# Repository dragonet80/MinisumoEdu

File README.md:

# MinisumoEdu
Robot de minisumo amb finalitats educatives.

De moment, hi ha els arxius en format Eagle de les plaques i les peces en 3D en format Sketchup.

Falten exemples software.
**Pendent de pujar tots els arxius i organitzar-ho tot**

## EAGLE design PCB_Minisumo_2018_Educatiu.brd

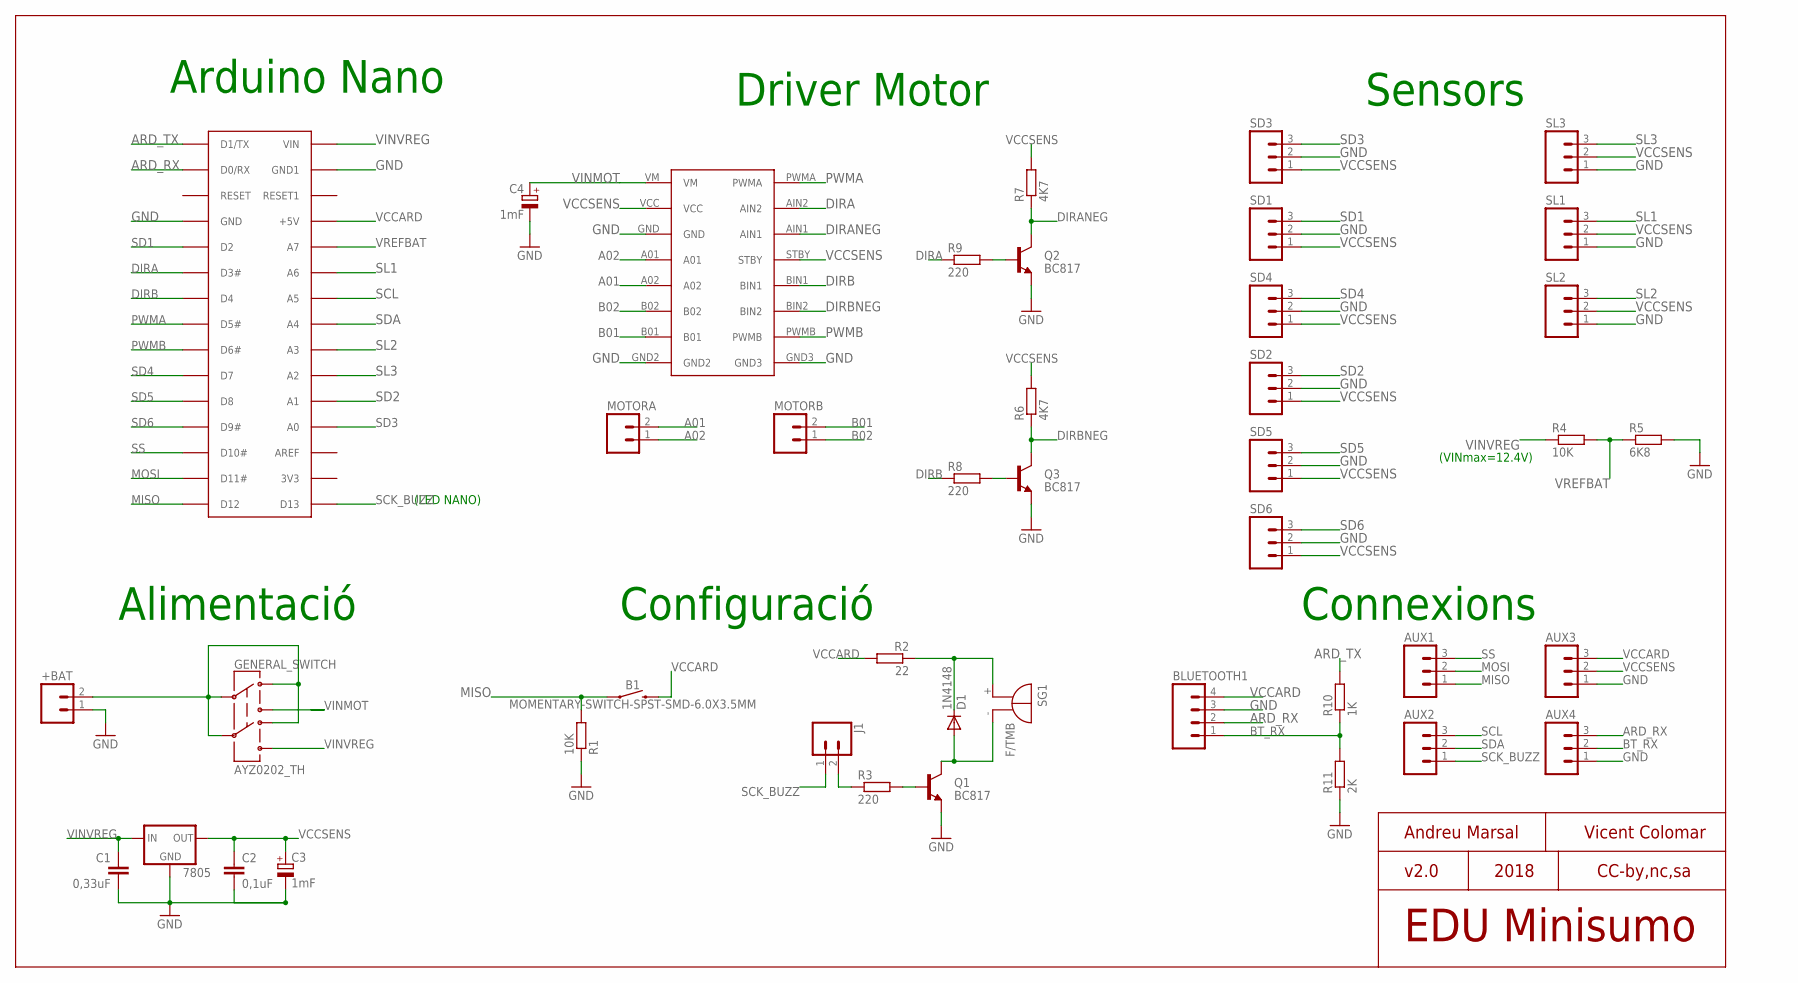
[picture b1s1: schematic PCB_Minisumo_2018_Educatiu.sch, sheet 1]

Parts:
7805: V_REG_78XXSINK; TO220-IGO
+BAT: M02LOCK_LONGPADS; 1X02_LOCK_LONGPADS
AUX1, AUX2, AUX3, AUX4: M03PTH; 1X03
B1: MOMENTARY-SWITCH-SPST-SMD-6.0X3.5MM; TACTILE_SWITCH_SMD_6.0X3.5MM
BLUETOOTH1: M04PTH; 1X04
C1: 0,33uF; C1206K
C2: 0,1uF; C1206K
C3, C4: 1mF; E2,5-6
D1: 1N4148; SOD106-R
GENERAL_SWITCH: AYZ0202_TH
J1: CONN_02; 1X02
MOTORA: M023.5MM; SCREWTERMINAL-3.5MM-2
MOTORB: M023.5MM; SCREWTERMINAL-3.5MM-2
Q1, Q2, Q3: BC817; TO-92
R1, R4: 10K; R1206
R2: 22; R1206
R3, R8, R9: 220; M1206
R5: 6K8; R1206
R6, R7: 4K7; M1206
R10: 1K; R1206
R11: 2K; R1206
SD1, SD2, SD3, SD4, SD5, SD6: M03PTH; 1X03
SG1: F/TMB
SL1, SL2, SL3: M03PTH; 1X03
U$1: ARDUINONANONOHOLES; PDIP-32NOHOLES
U$2: TB6612FNG_SPARKFUN

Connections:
A01: MOTORA.2, U$2.A02
A02: MOTORA.1, U$2.A01
ARD_RX: AUX4.3, BLUETOOTH1.2, U$1.D0/RX; also elsewhere on the board
ARD_TX: R10.2, U$1.D1/TX; also elsewhere on the board
B01: MOTORB.2, U$2.B01
B02: MOTORB.1, U$2.B02
BT_RX: AUX4.2, BLUETOOTH1.1, R10.1, R11.2
DIRA: R9.1, U$1.D3 (D3#), U$2.AIN2
DIRANEG: Q2.3 (C), R7.1, U$2.AIN1
DIRB: R8.1, U$1.D4, U$2.BIN1
DIRBNEG: Q3.3 (C), R6.1, U$2.BIN2
GND: 7805.GND, +BAT.1, AUX3.1, AUX4.1, BLUETOOTH1.3, C1.2, C2.2, C3.-, C4.-, Q1.1 (E), Q2.1 (E), Q3.1 (E), R1.1, R5.2, R11.1, SD1.2, SD2.2, SD3.2, SD4.2, SD5.2, SD6.2, SL1.1, SL2.1, SL3.1, U$1.GND, U$1.GND1, U$2.GND, U$2.GND2, U$2.GND3; also elsewhere on the board
MISO: AUX1.1, B1.1, R1.2, U$1.D12; also elsewhere on the board
MOSI: AUX1.2, U$1.D11 (D11#); also elsewhere on the board
unnamed: J1.2, R3.1
unnamed: Q1.2 (B), R3.2
unnamed: D1.A, Q1.3 (C), SG1.-
unnamed: Q2.2 (B), R9.2
unnamed: D1.C, R2.1, SG1.+
unnamed: Q3.2 (B), R8.2
PWMA: U$1.D5 (D5#), U$2.PWMA
PWMB: U$1.D6 (D6#), U$2.PWMB
SCK_BUZZ: AUX2.1, J1.1, U$1.D13; also elsewhere on the board
SCL: AUX2.3, U$1.A5; also elsewhere on the board
SD1: SD1.3, U$1.D2
SD2: SD2.3, U$1.A1
SD3: SD3.3, U$1.A0
SD4: SD4.3, U$1.D7
SD5: SD5.3, U$1.D8
SD6: SD6.3, U$1.D9 (D9#)
SDA: AUX2.2, U$1.A4; also elsewhere on the board
SL1: SL1.3, U$1.A6
SL2: SL2.3, U$1.A3
SL3: SL3.3, U$1.A2
SS: AUX1.3, U$1.D10 (D10#); also elsewhere on the board
VBAT: +BAT.2, GENERAL_SWITCH.C1, GENERAL_SWITCH.C2, GENERAL_SWITCH.D1, GENERAL_SWITCH.D2
VCCARD: AUX3.3, B1.2, BLUETOOTH1.4, R2.2, U$1.+5V; also elsewhere on the board
VCCSENS: 7805.OUT, AUX3.2, C2.1, C3.+, R6.2, R7.2, SD1.1, SD2.1, SD3.1, SD4.1, SD5.1, SD6.1, SL1.2, SL2.2, SL3.2, U$2.STBY, U$2.VCC; also elsewhere on the board
VINMOT: C4.+, GENERAL_SWITCH.B1, U$2.VM
VINVREG: 7805.IN, C1.1, GENERAL_SWITCH.B2, R4.1, U$1.VIN; also elsewhere on the board
VREFBAT: R4.2, R5.1, U$1.A7

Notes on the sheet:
Alimentació
Configuració
Arduino Nano
Driver Motor
(VINmax=12.4V)
Sensors
(LED NANO)
EDU Minisumo
v2.0
2018
CC-by,nc,sa
Andreu Marsal
Vicent Colomar
Connexions

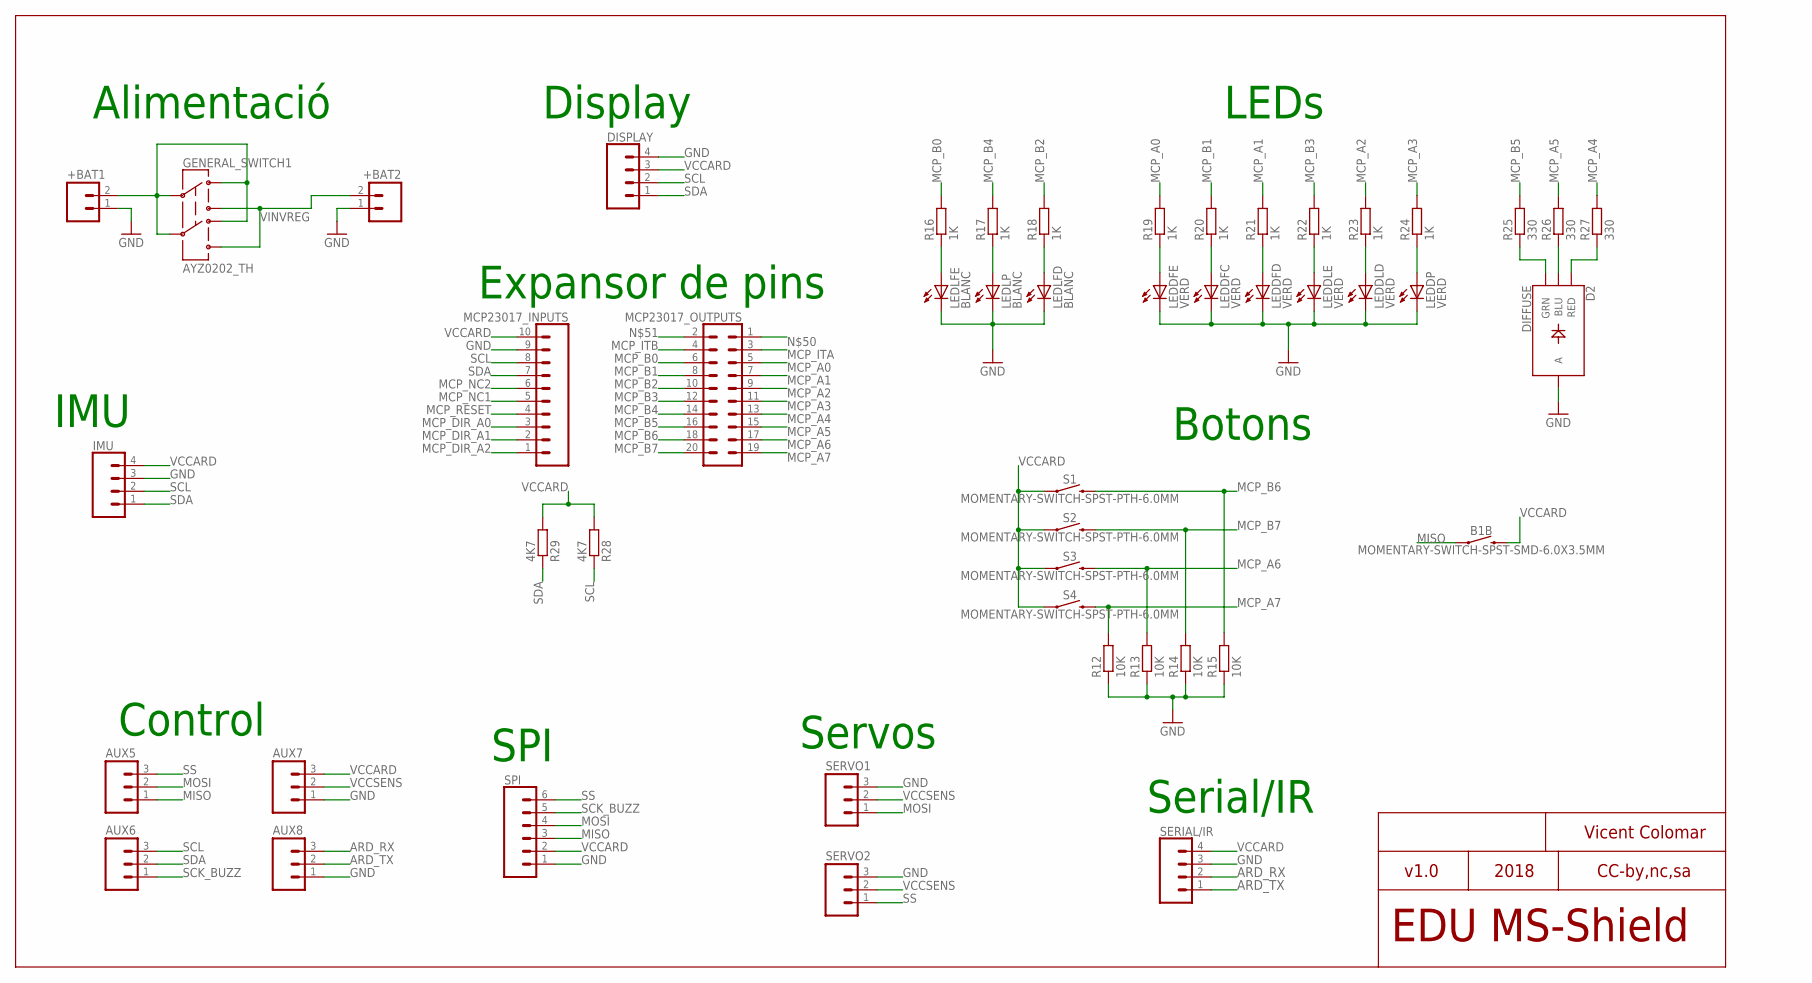
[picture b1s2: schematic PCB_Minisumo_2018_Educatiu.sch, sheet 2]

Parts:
+BAT1, +BAT2: M02LOCK_LONGPADS; 1X02_LOCK_LONGPADS
AUX5, AUX6, AUX7, AUX8: M03PTH; 1X03
B1B: MOMENTARY-SWITCH-SPST-SMD-6.0X3.5MM; TACTILE_SWITCH_SMD_6.0X3.5MM
D2: DIFFUSE; LED-RGB-THRU
DISPLAY: CONN_04; 1X04
GENERAL_SWITCH1: AYZ0202_TH
IMU: CONN_04; 1X04
LEDDFC: VERD; 1206
LEDDFD: VERD; 1206
LEDDFE: VERD; 1206
LEDDLD: VERD; 1206
LEDDLE: VERD; 1206
LEDDP: VERD; 1206
LEDLFD: BLANC; 1206
LEDLFE: BLANC; 1206
LEDLP: BLANC; 1206
MCP23017_INPUTS: CONN_10"; 1X10
MCP23017_OUTPUTS: CONN_10X2; 2X10
R12, R13, R14, R15: 10K; M1206
R16, R17, R18, R19, R20, R21, R22, R23, R24: 1K; M1206
R25, R26, R27: 330; M1206
R28, R29: 4K7; M1206
S1, S2, S3, S4: MOMENTARY-SWITCH-SPST-PTH-6.0MM; TACTILE_SWITCH_PTH_6.0MM
SERIAL/IR: CONN_04; 1X04
SERVO1, SERVO2: M03PTH; 1X03
SPI: CONN_06SILK_FEMALE_PTH; 1X06

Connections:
ARD_RX: AUX8.3, SERIAL/IR.2; also elsewhere on the board
ARD_TX: AUX8.2, SERIAL/IR.1; also elsewhere on the board
GND: +BAT1.1, +BAT2.1, AUX7.1, AUX8.1, D2.2 (A), DISPLAY.4, IMU.3, LEDDFC.C, LEDDFD.C, LEDDFE.C, LEDDLD.C, LEDDLE.C, LEDDP.C, LEDLFD.C, LEDLFE.C, LEDLP.C, MCP23017_INPUTS.9, R12.1, R13.1, R14.1, R15.1, SERIAL/IR.3, SERVO1.3, SERVO2.3, SPI.1; also elsewhere on the board
MCP_A0: MCP23017_OUTPUTS.5, R19.2
MCP_A1: MCP23017_OUTPUTS.7, R21.2
MCP_A2: MCP23017_OUTPUTS.9, R23.2
MCP_A3: MCP23017_OUTPUTS.11, R24.2
MCP_A4: MCP23017_OUTPUTS.13, R27.2
MCP_A5: MCP23017_OUTPUTS.15, R26.2
MCP_A6: MCP23017_OUTPUTS.17, R13.2, S3.3 (2)
MCP_A7: MCP23017_OUTPUTS.19, R12.2, S4.3 (2)
MCP_B0: MCP23017_OUTPUTS.6, R16.2
MCP_B1: MCP23017_OUTPUTS.8, R20.2
MCP_B2: MCP23017_OUTPUTS.10, R18.2
MCP_B3: MCP23017_OUTPUTS.12, R22.2
MCP_B4: MCP23017_OUTPUTS.14, R17.2
MCP_B5: MCP23017_OUTPUTS.16, R25.2
MCP_B6: MCP23017_OUTPUTS.18, R15.2, S1.3 (2)
MCP_B7: MCP23017_OUTPUTS.20, R14.2, S2.3 (2)
MCP_DIR_A0: MCP23017_INPUTS.3
MCP_DIR_A1: MCP23017_INPUTS.2
MCP_DIR_A2: MCP23017_INPUTS.1
MCP_ITA: MCP23017_OUTPUTS.3
MCP_ITB: MCP23017_OUTPUTS.4
MCP_NC1: MCP23017_INPUTS.5
MCP_NC2: MCP23017_INPUTS.6
MCP_RESET: MCP23017_INPUTS.4
MISO: AUX5.1, B1B.1, SPI.3; also elsewhere on the board
MOSI: AUX5.2, SERVO1.1, SPI.4; also elsewhere on the board
unnamed: D2.3 (GRN), R25.1
unnamed: LEDLFE.A, R16.1
unnamed: LEDLP.A, R17.1
unnamed: LEDLFD.A, R18.1
unnamed: LEDDFE.A, R19.1
unnamed: LEDDFC.A, R20.1
unnamed: LEDDFD.A, R21.1
unnamed: LEDDLE.A, R22.1
unnamed: LEDDLD.A, R23.1
unnamed: LEDDP.A, R24.1
unnamed: D2.4 (BLU), R26.1
unnamed: D2.1 (RED), R27.1
SCK_BUZZ: AUX6.1, SPI.5; also elsewhere on the board
SCL: AUX6.3, DISPLAY.2, IMU.2, MCP23017_INPUTS.8, R28.1; also elsewhere on the board
SDA: AUX6.2, DISPLAY.1, IMU.1, MCP23017_INPUTS.7, R29.1; also elsewhere on the board
SS: AUX5.3, SERVO2.1, SPI.6; also elsewhere on the board
VBAT1: +BAT1.2, GENERAL_SWITCH1.C1, GENERAL_SWITCH1.C2, GENERAL_SWITCH1.D1, GENERAL_SWITCH1.D2
VCCARD: AUX7.3, B1B.2, DISPLAY.3, IMU.4, MCP23017_INPUTS.10, R28.2, R29.2, S1.1, S2.1, S3.1, S4.1, SERIAL/IR.4, SPI.2; also elsewhere on the board
VCCSENS: AUX7.2, SERVO1.2, SERVO2.2; also elsewhere on the board
VINVREG: +BAT2.2, GENERAL_SWITCH1.B1, GENERAL_SWITCH1.B2; also elsewhere on the board

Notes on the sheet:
EDU MS-Shield
2018
CC-by,nc,sa
Vicent Colomar
Alimentació
Display
Expansor de pins
Control
Serial/IR
Servos
LEDs
Botons
IMU
v1.0
SPI

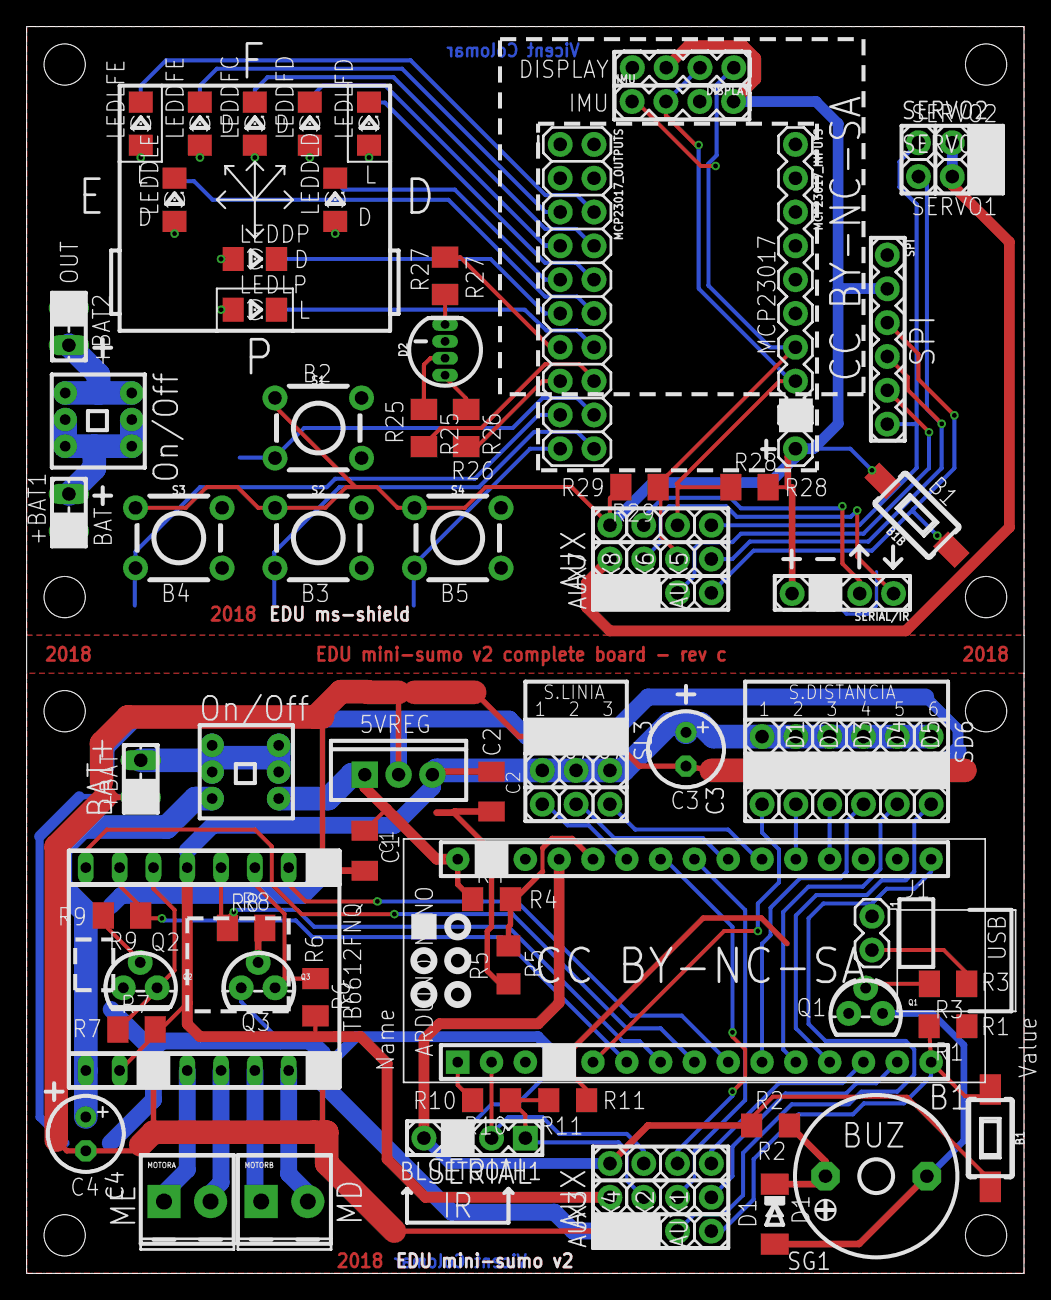
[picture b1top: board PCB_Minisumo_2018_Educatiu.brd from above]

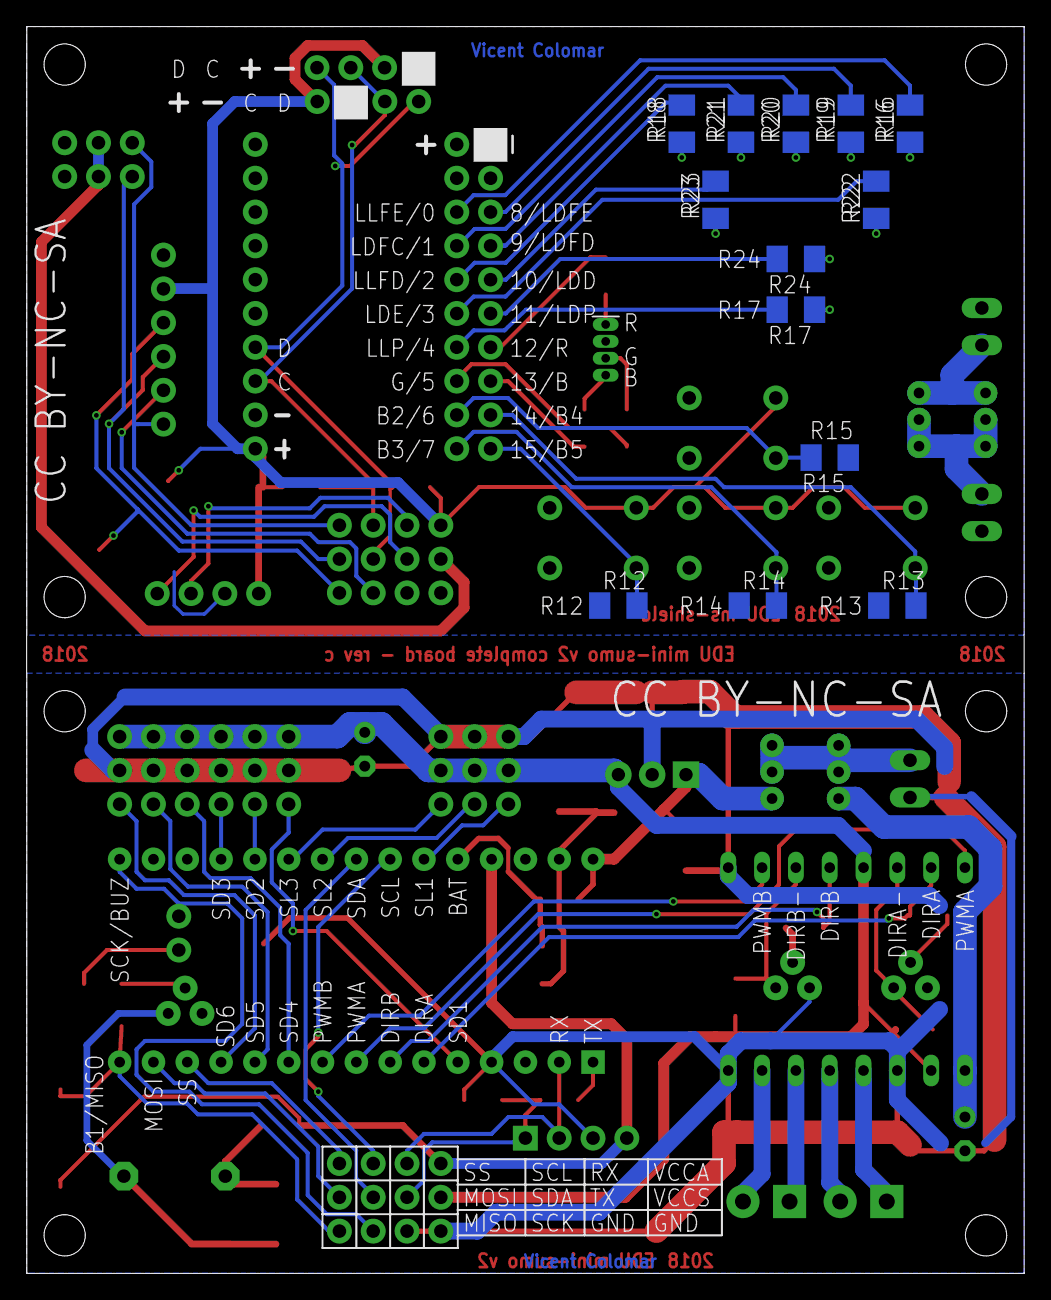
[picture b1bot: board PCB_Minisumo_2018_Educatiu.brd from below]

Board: 2 copper layers, 74.9 x 93.7 mm, 91 parts (13 on the bottom side), 70 nets.

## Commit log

2018-10-21 Create 3D-STL
2018-12-02 Add files via upload
    Corregits petits defectes en la placa.
2018-12-12 Carpeta documents
2019-02-02 Add files via upload
    Revisat i millorat el xassis.
2019-02-02 Create Programari
2019-05-25 Ja funciona correctament
    S'han d'ajustar els valors de velocitats i girs.

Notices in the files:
parts and their libraries:
SparkFun: Licensing: CC v3.0 Share-Alike You are welcome to use this library for commercial purposes.
SparkFun-Connectors: Licensing: Creative Commons ShareAlike 4.0 International - https://creativecommons.org/licenses/by-sa/4.0
